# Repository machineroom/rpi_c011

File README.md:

C011 based Transputer link interface for Raspberry Pi. Loopback performance with 20Mbps link on Rpi4 is ~11Mbps

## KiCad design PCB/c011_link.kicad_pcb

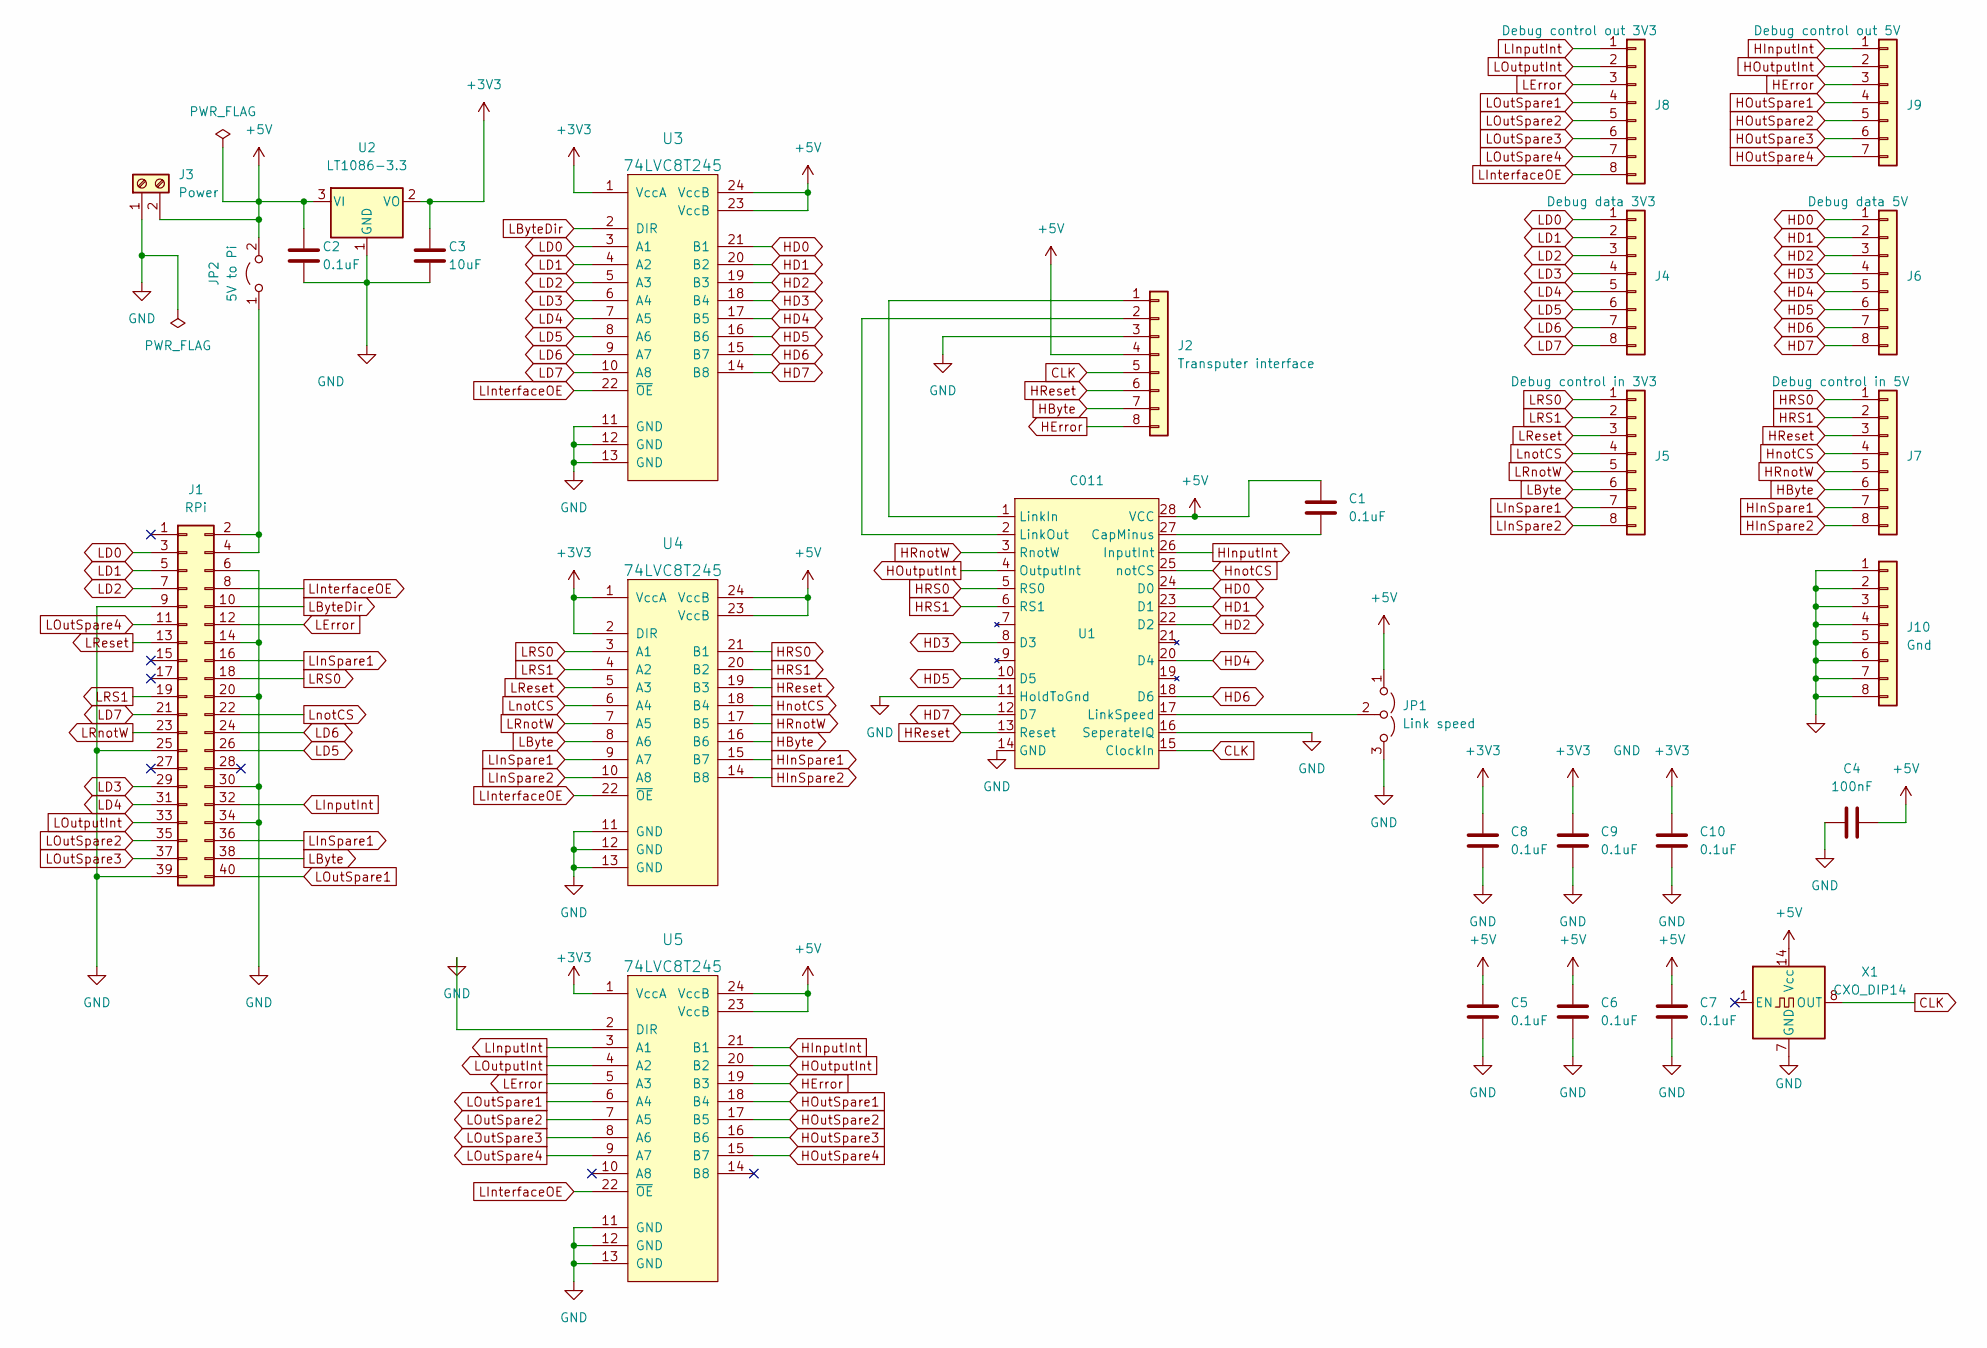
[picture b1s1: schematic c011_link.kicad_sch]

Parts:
C1, C2: 0.1uF; C_Disc_D5.0mm_W2.5mm_P5.00mm
C3: 10uF; CP_Radial_Tantal_D5.0mm_P2.50mm
C4: 100nF; C_Disc_D5.0mm_W2.5mm_P5.00mm
C5, C6, C7, C8, C9, C10: 0.1uF; C_0402_1005Metric_Pad0.74x0.62mm_HandSolder
J1: RPi; PinHeader_2x20_P2.54mm_Vertical
J2: Transputer interface; PinHeader_1x08_P2.54mm_Vertical
J3: Power; TerminalBlock_bornier-2_P5.08mm
J4: Debug data 3V3; PinHeader_1x08_P2.54mm_Vertical
J5: Debug control in 3V3; PinHeader_1x08_P2.54mm_Vertical
J6: Debug data 5V; PinHeader_1x08_P2.54mm_Vertical
J7: Debug control in 5V; PinHeader_1x08_P2.54mm_Vertical
J8: Debug control out 3V3; PinHeader_1x08_P2.54mm_Vertical
J9: Debug control out 5V; PinHeader_1x07_P2.54mm_Vertical
J10: Gnd; PinHeader_1x08_P2.54mm_Vertical
JP1: Link speed; PinHeader_1x03_P2.54mm_Vertical
JP2: 5V to Pi; PinHeader_1x02_P2.54mm_Vertical
U1: C011; DIP-28_W15.24mm
U2: LT1086-3.3; TO-220-3_Horizontal_TabDown
U3, U4, U5: 74LVC8T245; SOIC-24W_7.5x15.4mm_P1.27mm
X1: CXO_DIP14; Oscillator_DIP-14

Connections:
+3V3: C3.1, C8.1, C9.1, C10.1, U2.2 (VO), U3.1 (VccA), U4.1 (VccA), U4.2 (DIR), U5.1 (VccA)
+5V: C1.1, C2.1, C4.1, C5.1, C6.1, C7.1, J2.4, J3.2, JP1.1 (A), JP2.2 (B), U1.28 (VCC), U2.3 (VI), U3.23 (VccB), U3.24 (VccB), U4.23 (VccB), U4.24 (VccB), U5.23 (VccB), U5.24 (VccB), X1.14 (Vcc)
CLK: J2.5, U1.15 (ClockIn), X1.8 (OUT)
GND: C2.2, C3.2, C4.2, C5.2, C6.2, C7.2, C8.2, C9.2, C10.2, J1.6, J1.9, J1.14, J1.20, J1.25, J1.30, J1.34, J1.39, J2.3, J3.1, J10.1, J10.2, J10.3, J10.4, J10.5, J10.6, J10.7, J10.8, JP1.3 (B), U1.11 (HoldToGnd), U1.14 (GND), U1.16 (SeperateIQ), U2.1 (GND), U3.11 (GND), U3.12 (GND), U3.13 (GND), U4.11 (GND), U4.12 (GND), U4.13 (GND), U5.2 (DIR), U5.11 (GND), U5.12 (GND), U5.13 (GND), X1.7 (GND)
HByte: J2.7, J7.6, U4.16 (B6)
HD0: J6.1, U1.24 (D0), U3.21 (B1)
HD1: J6.2, U1.23 (D1), U3.20 (B2)
HD2: J6.3, U1.22 (D2), U3.19 (B3)
HD3: J6.4, U1.8 (D3), U3.18 (B4)
HD4: J6.5, U1.20 (D4), U3.17 (B5)
HD5: J6.6, U1.10 (D5), U3.16 (B6)
HD6: J6.7, U1.18 (D6), U3.15 (B7)
HD7: J6.8, U1.12 (D7), U3.14 (B8)
HError: J2.8, J9.3, U5.19 (B3)
HInSpare1: J7.7, U4.15 (B7)
HInSpare2: J7.8, U4.14 (B8)
HInputInt: J9.1, U1.26 (InputInt), U5.21 (B1)
HOutSpare1: J9.4, U5.18 (B4)
HOutSpare2: J9.5, U5.17 (B5)
HOutSpare3: J9.6, U5.16 (B6)
HOutSpare4: J9.7, U5.15 (B7)
HOutputInt: J9.2, U1.4 (OutputInt), U5.20 (B2)
HRS0: J7.1, U1.5 (RS0), U4.21 (B1)
HRS1: J7.2, U1.6 (RS1), U4.20 (B2)
HReset: J2.6, J7.3, U1.13 (Reset), U4.19 (B3)
HRnotW: J7.5, U1.3 (RnotW), U4.17 (B5)
HnotCS: J7.4, U1.25 (notCS), U4.18 (B4)
LByte: J1.38, J5.6, U4.8 (A6)
LByteDir: J1.10, U3.2 (DIR)
LD0: J1.3, J4.1, U3.3 (A1)
LD1: J1.5, J4.2, U3.4 (A2)
LD2: J1.7, J4.3, U3.5 (A3)
LD3: J1.29, J4.4, U3.6 (A4)
LD4: J1.31, J4.5, U3.7 (A5)
LD5: J1.26, J4.6, U3.8 (A6)
LD6: J1.24, J4.7, U3.9 (A7)
LD7: J1.21, J4.8, U3.10 (A8)
LError: J1.12, J8.3, U5.5 (A3)
LInSpare1: J1.16, J1.36, J5.7, U4.9 (A7)
LInSpare2: J5.8, U4.10 (A8)
LInputInt: J1.32, J8.1, U5.3 (A1)
LInterfaceOE: J1.8, J8.8, U3.22 (~OE), U4.22 (~OE), U5.22 (~OE)
LOutSpare1: J1.40, J8.4, U5.6 (A4)
LOutSpare2: J1.35, J8.5, U5.7 (A5)
LOutSpare3: J1.37, J8.6, U5.8 (A6)
LOutSpare4: J1.11, J8.7, U5.9 (A7)
LOutputInt: J1.33, J8.2, U5.4 (A2)
LRS0: J1.18, J5.1, U4.3 (A1)
LRS1: J1.19, J5.2, U4.4 (A2)
LReset: J1.13, J5.3, U4.5 (A3)
LRnotW: J1.23, J5.5, U4.7 (A5)
LnotCS: J1.22, J5.4, U4.6 (A4)
unnamed: C1.2, U1.27 (CapMinus)
unnamed: J1.2, J1.4, JP2.1 (A)
unnamed: J2.1, U1.1 (LinkIn)
unnamed: J2.2, U1.2 (LinkOut)
unnamed: JP1.2 (C), U1.17 (LinkSpeed)

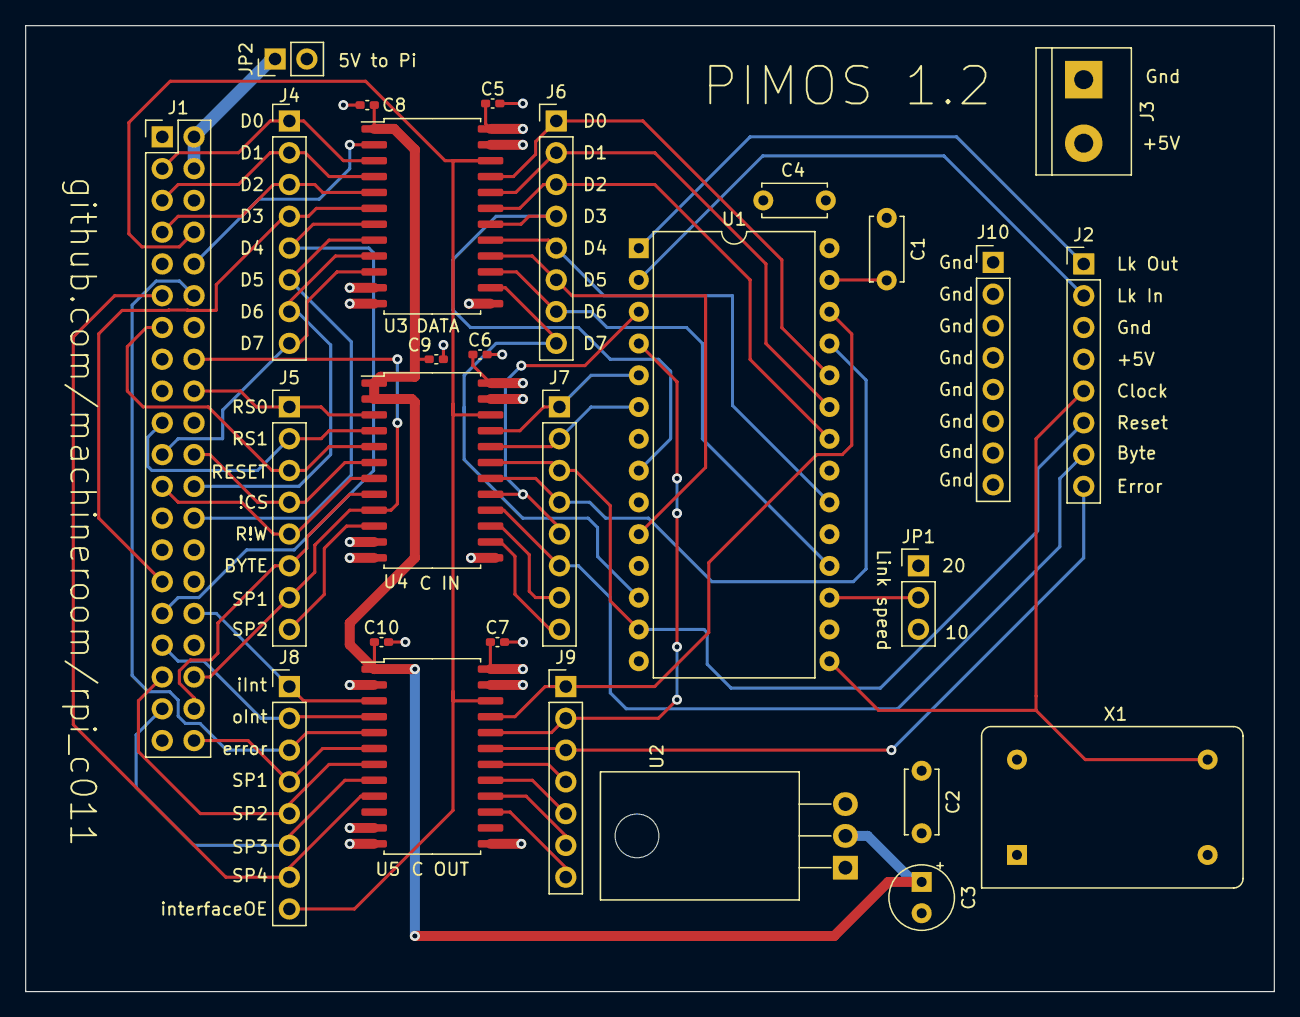
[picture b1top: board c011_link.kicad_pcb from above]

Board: 4 copper layers, 99.8 x 77.2 mm, 28 parts (0 on the bottom side), 57 nets.

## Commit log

2019-09-03 First test of RPI based C011 interface
2019-09-21 Add byte writing
2019-09-22 C011 loopback test working
2019-09-26 tighten up timing
2019-09-26 move c011 to library. added bootstrap. loopback OK if TRAM not powered and not comsuming clock. needs clock boost + seperate PSU for TRAM
2019-09-28 Add more delays - boot of T425 sometimes works
2019-09-29 longer reset pulse
2019-09-29 timeout on read to know how many bytes are read from link
2019-10-04 Add analyse and write timeout
2022-01-01 new rpi/c011 interface as per T-Mandel
2022-01-01 nanosleep isn't a thing
2022-01-08 Added PCB files
2022-01-08 Added readme
2022-01-08 Ignore boot exe
2022-01-08 Use cmake
2022-01-15 Add timing notes
2022-01-15 sync with T-Mandel for C++ compat
2022-01-15 implement a better ns sleep
2022-01-16 useful config for sigrok analyser
2022-01-16 sync with T-Mandel
2022-01-26 better c011 write timeout to match read timeout
2022-01-29 Add link pin to pulseview
2022-01-29 loopback with AA,55 checkerboard OK
2022-02-01 Debugging odd isses with loopback. some byte values cause link lockup
2022-02-01 Record all failed byte values
2022-02-01 more options for c011 loopback testing
2022-02-04 resolving random incorrect bytes with good power
2022-02-04 Add random byte value test to loopback test
2022-02-04 dump erf stats. 2.6Mb/sec
2022-02-04 use non barrier reg access, 3.5Mb/sec
2022-02-04 ns sleep (sort of). 6.3 Mb/sec
2022-02-04 print total bytes in loopback
2022-02-05 Update to PCB 1.1 design
2022-03-06 new pulseview config
2022-03-12 Use BYTE output as error indicator for c011 testing
2022-03-12 debug random bits set in boot return
2022-03-12 faffing
2022-03-19 Bootstrap testing now works OK with no ribbon cable from pi to c011
2022-03-19 6Mbps seems mostly reliable on loopback and boot
2022-03-19 move to 74LVC8T245 level converters
    The existing auto detecting direction shifters can glitch into the 'wrong' direction
2022-04-10 use _nb versions for slight performance boost
2022-04-10 only set level shifter direction if required
2022-04-10 remove all sleeps from c011 code. loopback 10.1Mbps
2022-04-10 Add status flag checks - required by ispy
2022-04-10 typo
2022-05-02 set byte mode when testing boot
2022-12-20 more test variants
2022-12-29 move all wx specific stuff out of c011 driver
2023-03-26 dump devid
2024-01-06 First working loopback on rpi5. 0.5Mbps
2024-01-06 rm dep on bcm2835 lib
2024-01-07 corect perf measure
2024-01-07 tidy
2024-01-07 Not using TXS0108
2024-01-07 Optimise direction switching. 11.8Mbits/sec
2024-01-07 fix compile with g++
2024-01-07 more C++ fixes
2024-01-14 start read/write timeout
2024-01-14 fix input/output setting
2024-03-14 fix compile error
2024-03-15 debugging
2024-03-15 fix read from c011. boot test works
2024-03-15 rm non-rp1 support
2024-03-15 Fix direction setting
2024-03-17 Set data pins as GPIO function
